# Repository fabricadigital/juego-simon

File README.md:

# juego-simon
Juego Simon para los talleres de electrónica y diseño de circuitos

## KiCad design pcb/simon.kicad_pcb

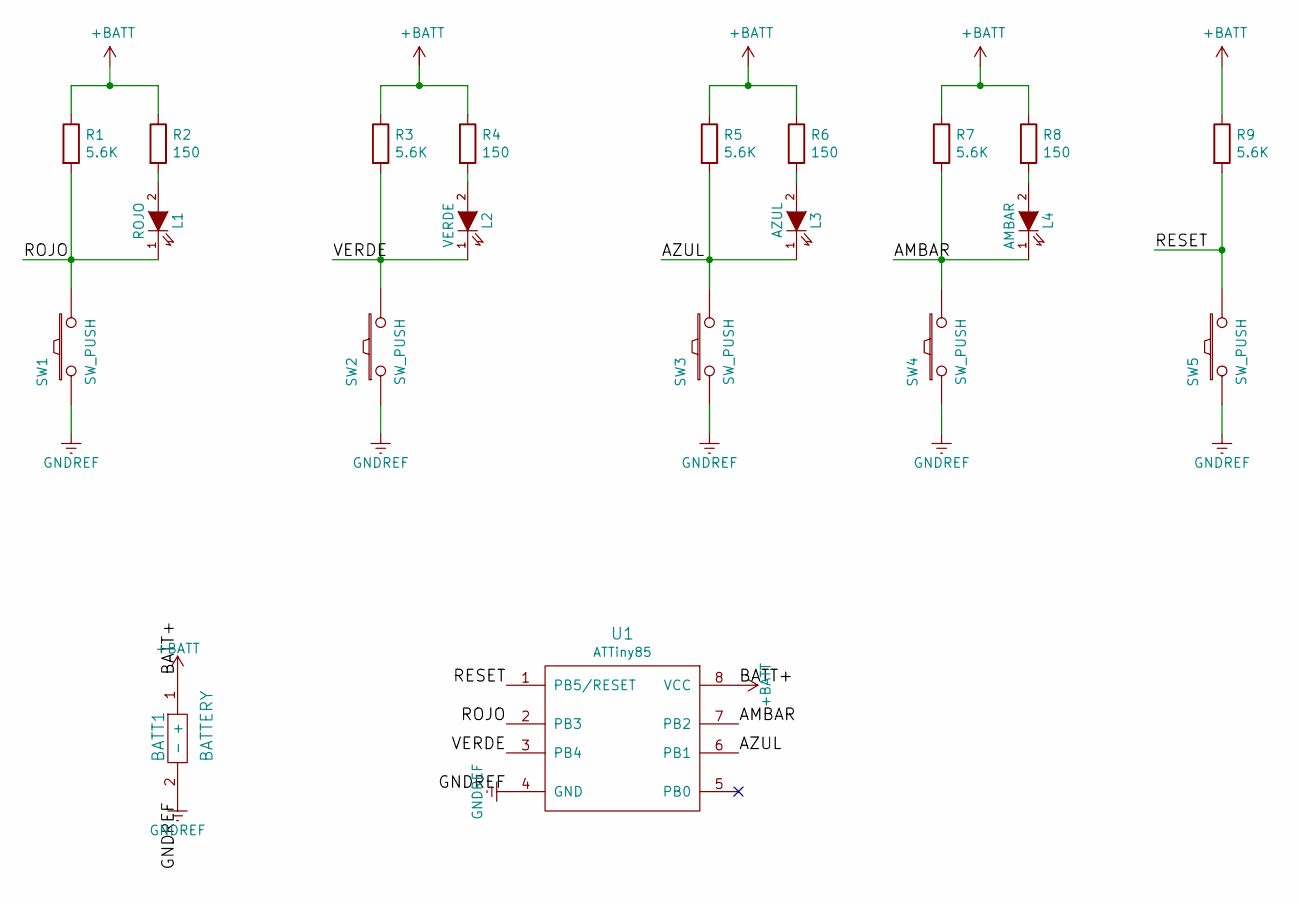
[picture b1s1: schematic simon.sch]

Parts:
BATT1: BATTERY
L1: ROJO; LED-5MM
L2: VERDE; LED-5MM
L3: AZUL; LED-5MM
L4: AMBAR; LED-5MM
R1, R3, R5, R7, R9: 5.6K; Resistor_Horizontal_RM7mm
R2, R4, R6, R8: 150; Resistor_Horizontal_RM7mm
SW1, SW2, SW3, SW4, SW5: SW_PUSH; button-sw-push
U1: ATTiny85; DIP-8_W7.62mm

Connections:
+BATT: BATT1.1 (+), R1.1, R2.1, R3.1, R4.1, R5.1, R6.1, R7.1, R8.1, R9.1, U1.8 (VCC)
/AMBAR: L4.1 (K), R7.2, SW4.2, U1.7 (PB2)
/AZUL: L3.1 (K), R5.2, SW3.2, U1.6 (PB1)
/RESET: R9.2, SW5.2, U1.1 (PB5/RESET)
/ROJO: L1.1 (K), R1.2, SW1.2, U1.2 (PB3)
/VERDE: L2.1 (K), R3.2, SW2.2, U1.3 (PB4)
GNDREF: BATT1.2 (-), SW1.1, SW2.1, SW3.1, SW4.1, SW5.1, U1.4 (GND)
unnamed: L1.2 (A), R2.2
unnamed: L2.2 (A), R4.2
unnamed: L3.2 (A), R6.2
unnamed: L4.2 (A), R8.2

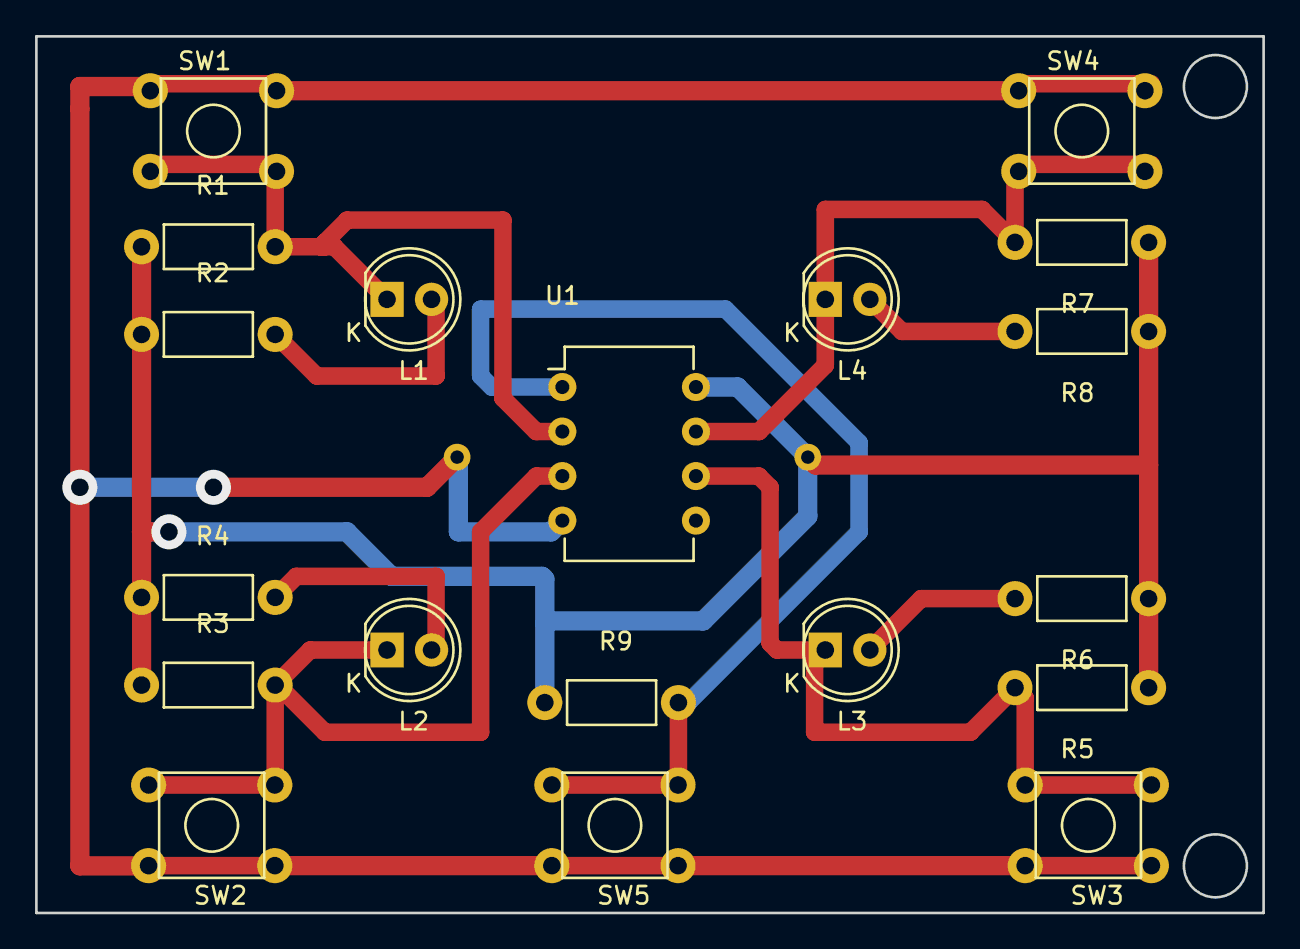
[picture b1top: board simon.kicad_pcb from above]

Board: 2 copper layers, 70.0 x 50.0 mm, 20 parts (1 on the bottom side), 11 nets.

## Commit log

2018-09-27 Primera versión
